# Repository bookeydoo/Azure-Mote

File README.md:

Azure-Mote

Azure-Mote is my submission for the KiCad 2026 PCB Design Competition. It is a standalone subsystem of a larger project currently in development—a modular handheld gaming device.

The Azure-Mote is a detachable Bluetooth Low Energy (BLE) controller designed to provide a seamless wireless gaming experience. It is built around the MDBT50Q-1MV2 module, enabling low-power Bluetooth connectivity while allowing the controller to be freely connected and disconnected from the main device using magnetic POGO-Pins.

When docked, the controller can be recharged directly through the handheld using the BQ24074RGT battery charger IC, eliminating the need for a separate charging solution and providing a convenient, integrated user experience.

Features:

-Bluetooth Low Energy (BLE) wireless controller.

-Built around the MDBT50Q-1MV2 Nordic-based BLE module

-Detachable design for flexible use and portability

-Integrated battery charging using the BQ24074RGT charger IC

-Dock-and-charge functionality when connected to the main handheld device

-Designed as part of a modular handheld gaming ecosystem

Project Status

Azure-Mote is a prototype needs proper testing and represents one component of a larger handheld gaming platform under active development. This submission focuses on the PCB design and hardware implementation of the controller module.

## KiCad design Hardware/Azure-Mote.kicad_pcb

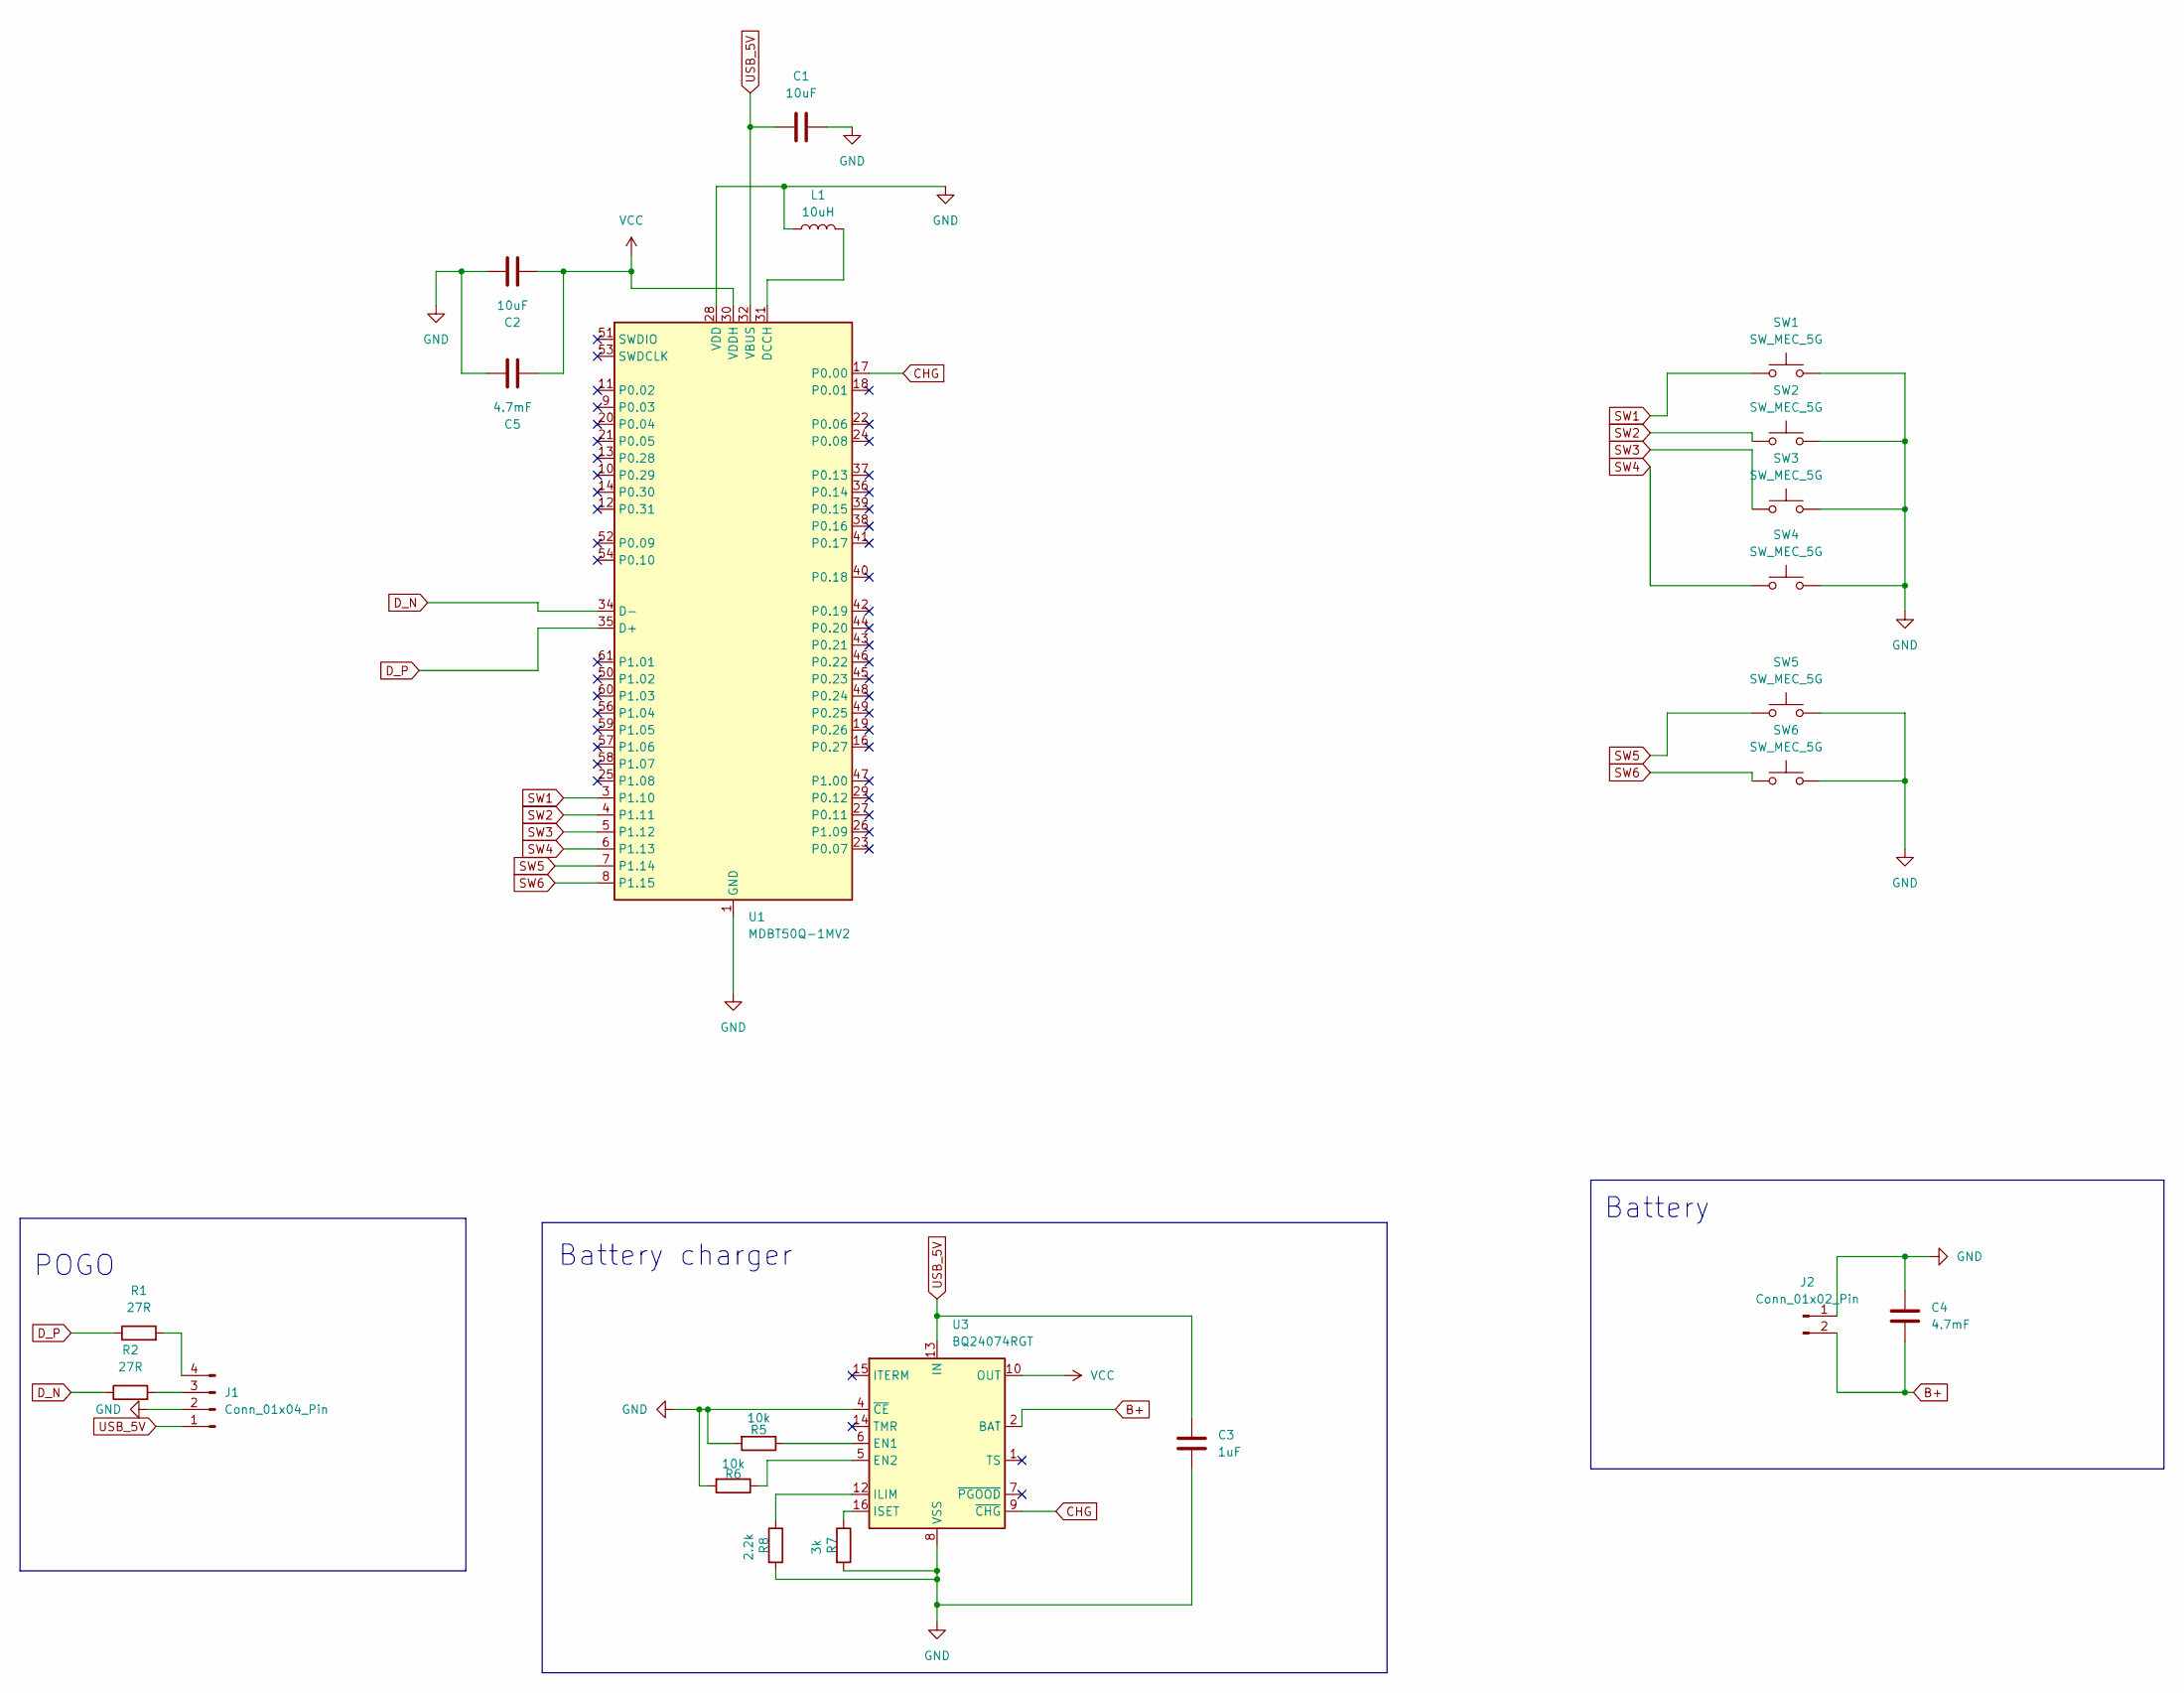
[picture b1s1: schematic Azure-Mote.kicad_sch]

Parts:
C1, C2: 10uF; C_0603_1608Metric
C3: 1uF; C_0603_1608Metric
C4, C5: 4.7mF; C_0603_1608Metric
J1: Conn_01x04_Pin; PinHeader_1x04_P1.27mm_Horizontal
J2: Conn_01x02_Pin; TestPoint_2Pads_Pitch2.54mm_Drill0.8mm
L1: 10uH; L_Changjiang_FNR4026S
R1, R2: 27R; R_0603_1608Metric_Pad0.98x0.95mm_HandSolder
R5, R6: 10k; R_0603_1608Metric_Pad0.98x0.95mm_HandSolder
R7: 3k; R_0603_1608Metric_Pad0.98x0.95mm_HandSolder
R8: 2.2k; R_0603_1608Metric_Pad0.98x0.95mm_HandSolder
SW1, SW2, SW3, SW4, SW5, SW6: SW_MEC_5G; SW_Push_1P1T_NO_CK_KSC7xxJ
U1: MDBT50Q-1MV2; Raytac_MDBT50Q
U3: BQ24074RGT; VQFN-16-1EP_3x3mm_P0.5mm_EP1.6x1.6mm

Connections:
B+: C4.1, J2.2, U3.2 (BAT), U3.3 (BAT)
CHG: U1.17 (P0.00), U3.9 (~CHG)
D_N: R2.1, U1.34 (D-)
D_P: R1.1, U1.35 (D+)
GND: C1.1, C2.1, C3.1, C4.2, C5.1, J1.2, J2.1, L1.1, R5.2, R6.2, R7.2, R8.2, SW1.3 (B), SW1.4 (B), SW2.3 (B), SW2.4 (B), SW3.3 (B), SW3.4 (B), SW4.3 (B), SW4.4 (B), SW5.3 (B), SW5.4 (B), SW6.3 (B), SW6.4 (B), U1.1 (GND), U1.2 (GND), U1.15 (GND), U1.28 (VDD), U1.33 (GND), U1.55 (GND), U3.4 (~CE), U3.8 (VSS), U3.17 (VSS)
unnamed: J1.3, R2.2
unnamed: J1.4, R1.2
unnamed: L1.2, U1.31 (DCCH)
unnamed: R5.1, U3.6 (EN1)
unnamed: R6.1, U3.5 (EN2)
unnamed: R8.1, U3.12 (ILIM)
unnamed: R7.1, U3.16 (ISET)
SW1: SW1.1 (A), SW1.2 (A), U1.3 (P1.10)
SW2: SW2.1 (A), SW2.2 (A), U1.4 (P1.11)
SW3: SW3.1 (A), SW3.2 (A), U1.5 (P1.12)
SW4: SW4.1 (A), SW4.2 (A), U1.6 (P1.13)
SW5: SW5.1 (A), SW5.2 (A), U1.7 (P1.14)
SW6: SW6.1 (A), SW6.2 (A), U1.8 (P1.15)
USB_5V: C1.2, C3.2, J1.1, U1.32 (VBUS), U3.13 (IN)
VCC: C2.2, C5.2, U1.30 (VDDH), U3.10 (OUT), U3.11 (OUT)

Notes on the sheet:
Battery
Battery charger
POGO

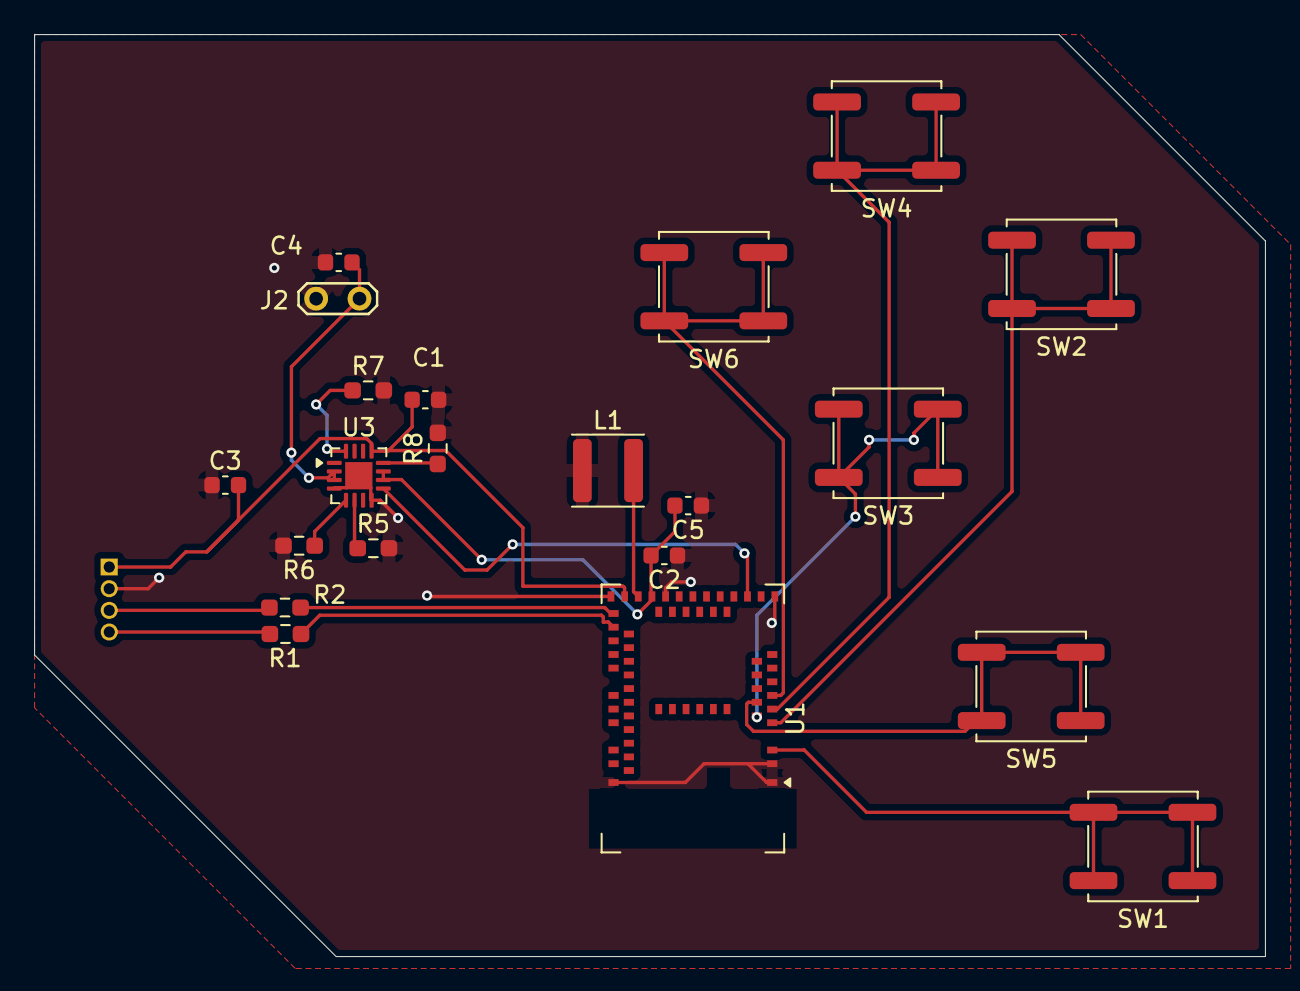
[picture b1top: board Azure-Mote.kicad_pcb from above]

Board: 2 copper layers, 72.1 x 54.0 mm, 22 parts (1 on the bottom side), 20 nets.

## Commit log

2026-06-14 readme
2026-06-14 hardware added
